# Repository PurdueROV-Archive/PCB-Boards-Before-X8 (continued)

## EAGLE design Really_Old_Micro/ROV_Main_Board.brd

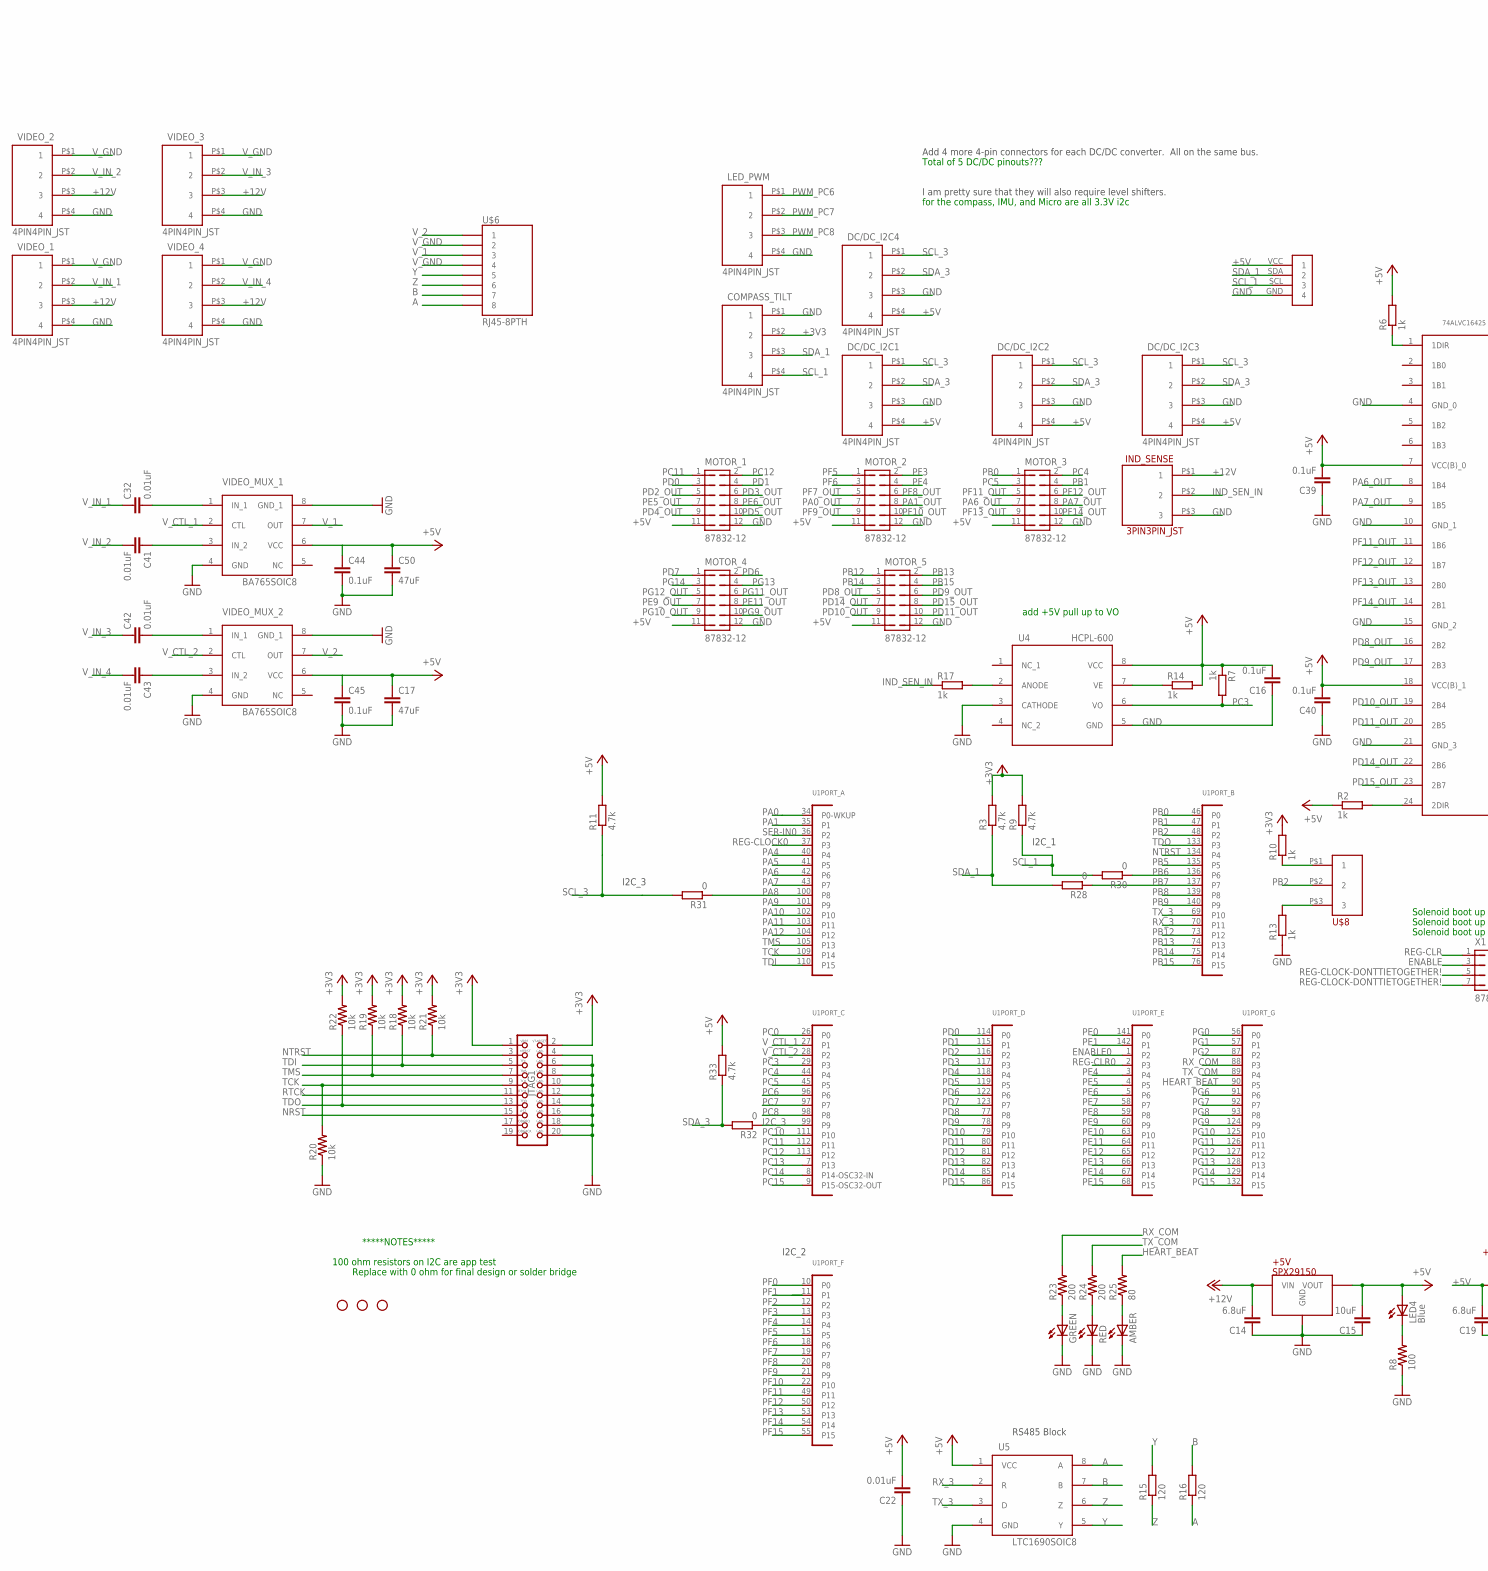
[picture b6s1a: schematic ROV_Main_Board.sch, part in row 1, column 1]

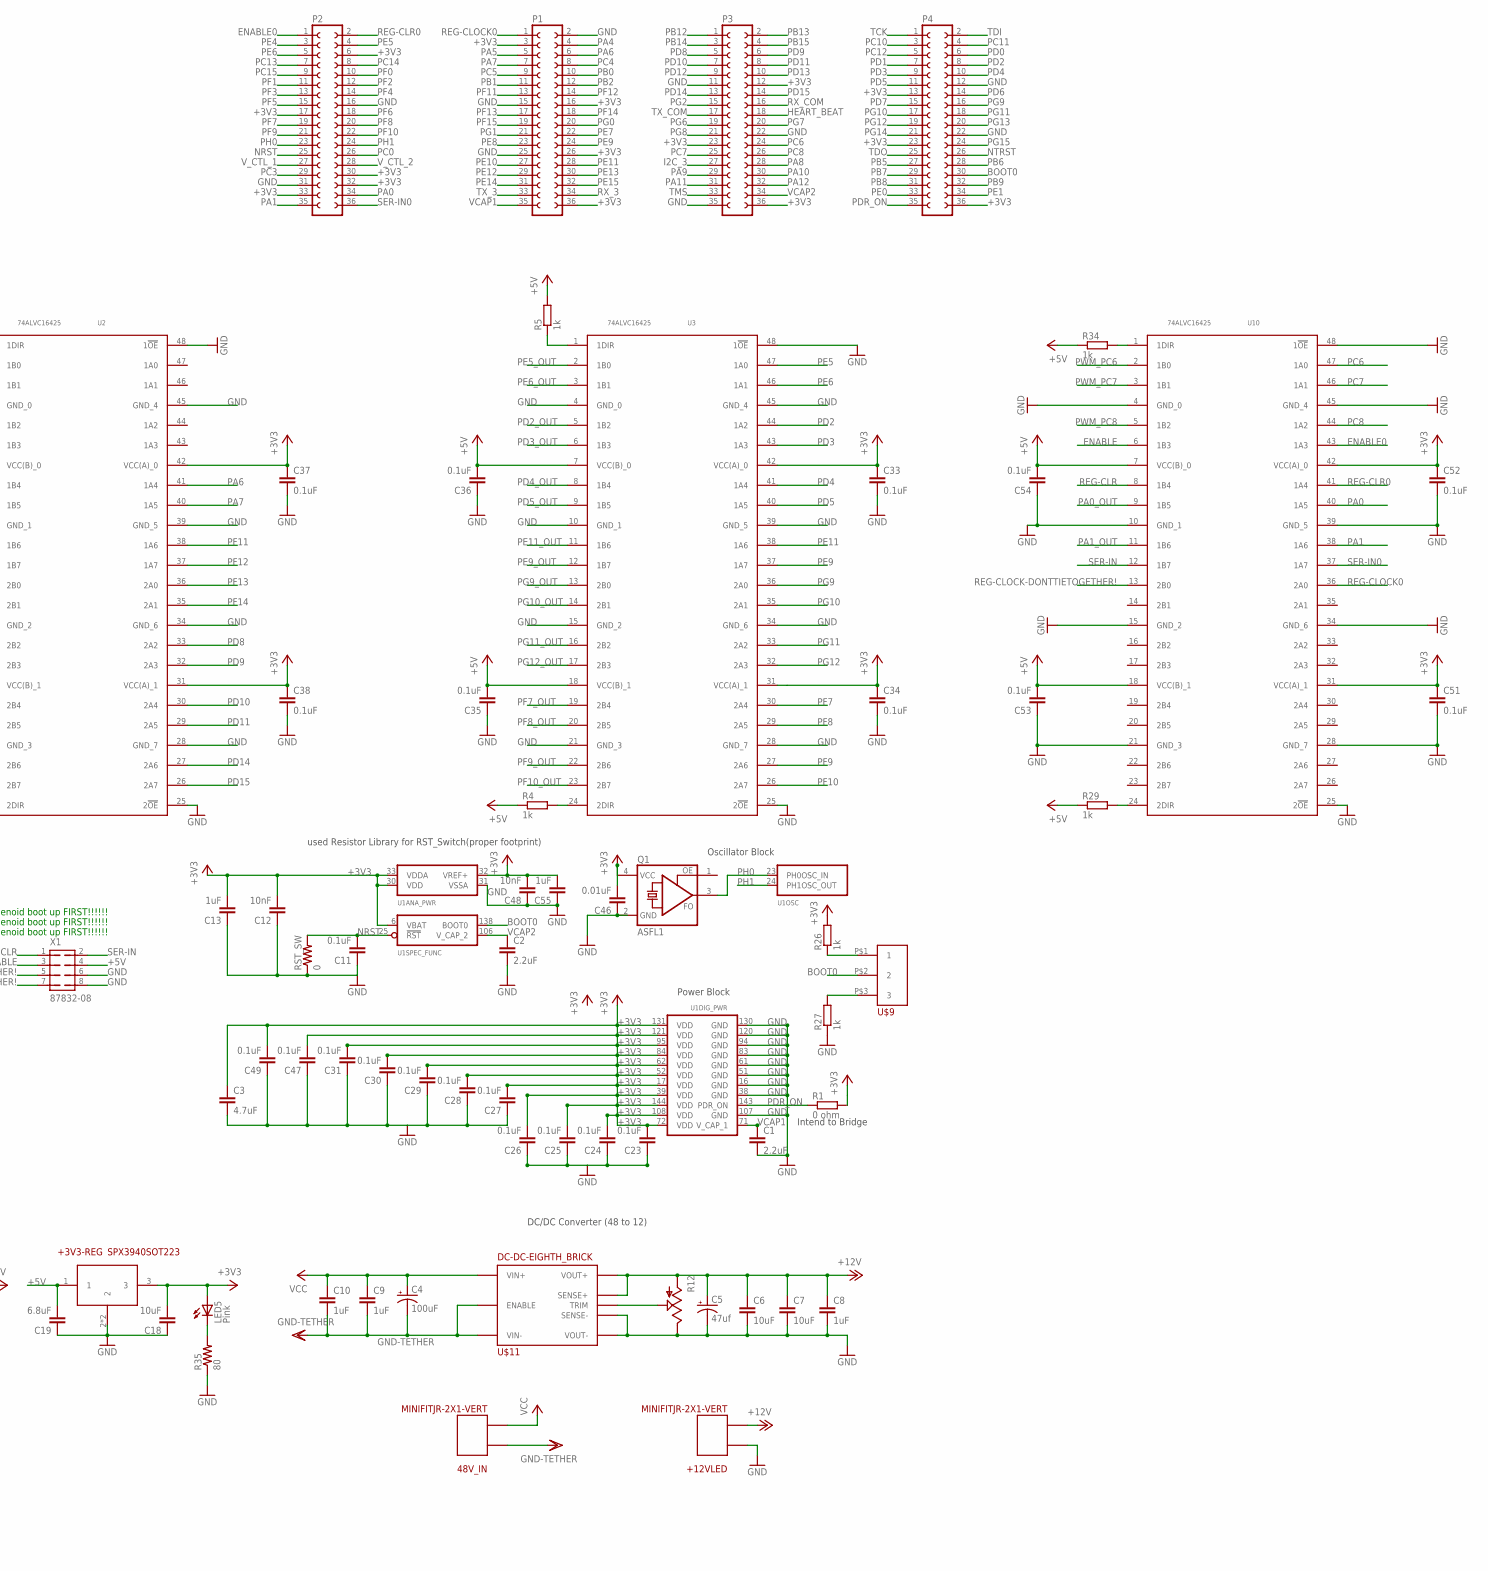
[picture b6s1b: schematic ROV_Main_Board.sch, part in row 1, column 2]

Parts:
48V_IN: MINIFITJR-2X1-VERT; 5566-02B
+3V3-REG: SPX3940SOT223; SOT223
+5V: SPX29150; DDPAK-3PIN
+12VLED: MINIFITJR-2X1-VERT; 5566-02B
AMBER: LED0603; LED-0603
C1, C2: 2.2uF; C0603; PARTNO 587-1263-1-ND
C3: 4.7uF; C0603; PARTNO 587-2786-1-ND
C4: 100uF; E5-10,5; PARTNO 493-1668-ND
C5: 47uf; PANASONIC_D; PARTNO PCE3929CT-ND
C6, C7, C15, C18: 10uF; C0805; PARTNO 587-2985-1-ND
C8, C9, C10: 1uF; C0805; PARTNO 445-5205-1-ND
C11, C16, C23, C24, C25, C26, C27, C28, C29, C30, C31, C33, C34, C35, C36, C37, C38, C39, C40, C44, C45, C47, C49, C51, C52, C53, C54: 0.1uF; C0603; PARTNO 311-1344-1-ND
C12, C48: 10nF; C0603; PARTNO 478-1227-1-ND
C13, C55: 1uF; C0603; PARTNO 445-5205-1-ND
C14, C19: 6.8uF; C0805; PARTNO 445-5982-1-ND
C17, C50: 47uF; C1206; PARTNO 490-5528-1-ND
C22, C32, C41, C42, C43, C46: 0.01uF; C0603; PARTNO 478-1227-1-ND
COMPASS_TILT: 4PIN4PIN_JST; 4PIN_JST; PARTNO 455-1659-ND
DC/DC_I2C1, DC/DC_I2C2, DC/DC_I2C3, DC/DC_I2C4: 4PIN4PIN_JST; 4PIN_JST; PARTNO 455-1659-ND
GREEN: LED0603; LED-0603
IND_SENSE: 3PIN3PIN_JST; 3PIN_JST; PARTNO 455-1658-ND
JP1, JP2, JP3: STAND-OFF
JTAG1: JTAG-ARM; PARTNO S9172-ND
LED4: Blue; LED-0603
LED5: Pink; LED-0603
LED_PWM: 4PIN4PIN_JST; 4PIN_JST; PARTNO 455-1659-ND
MOTOR_1, MOTOR_2, MOTOR_3, MOTOR_4, MOTOR_5: 87832-12; PARTNO WM18640-ND
P1, P2, P3, P4: FE18-2
Q1: ASFL1; ASF
R1: 0 ohm; R0603
R2, R4, R5, R6, R7, R10, R13, R14, R17, R26, R27, R29, R34: 1k; R0603
R3, R9, R11, R33: 4.7k; R0603
R8: 100; 0603-RES
R12: TRIM_US-SM-42/43W; SM-42/43W
R15, R16: 120; R0603
R18, R19, R20, R21, R22: 10k; R0603
R23, R24: 200; R0603
R25: 80; R0603
R28, R30, R31, R32: 0; R0603
R35: 80; 0603-RES
RED: LED0603; LED-0603
RST_SW: 0; R2512
U1: STM32F103ZESTM32F407; SQFP-S-20X20-144
U2, U3, U10: 74ALVC16425; TSSOP48
U4: HCPL-600; SOIC8
U5: LTC1690SOIC8; SOIC8
U$6: RJ45-8PTH; RJ45-8
U$7: 9DOF-IMU-SFE; 9DOF-SFE
U$8, U$9: 1X3-SMD-1.27MM; 1X3-1.27-SMD
U$11: DC-DC-EIGHTH_BRICK; EIGHTH-BRICK
VIDEO_1, VIDEO_2, VIDEO_3, VIDEO_4: 4PIN4PIN_JST; 4PIN_JST
VIDEO_MUX_1, VIDEO_MUX_2: BA765SOIC8; SOIC8
X1: 87832-08

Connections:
+3V3: +3V3-REG.3, C3.1, C12.2, C13.2, C18.2, C23.2, C24.2, C25.2, C26.2, C27.2, C28.2, C29.2, C30.2, C31.2, C33.1, C34.1, C37.1, C38.1, C46.2, C47.2, C48.2, C49.2, C51.1, C52.1, C55.2, COMPASS_TILT.P$2 (2), JTAG1.1, JTAG1.2, LED5.A, P1.3, P1.16, P1.26, P1.36, P2.6, P2.17, P2.30, P2.32, P2.33, P3.12, P3.23, P3.36, P4.13, P4.23, P4.36, Q1.4 (VCC), R1.2, R3.2, R9.2, R10.2, R18.2, R19.2, R21.2, R22.2, R26.2, U1.6 (VBAT), U1.17 (VDD), U1.30 (VDD), U1.32 (VREF+), U1.33 (VDDA), U1.39 (VDD), U1.52 (VDD), U1.62 (VDD), U1.72 (VDD), U1.84 (VDD), U1.95 (VDD), U1.108 (VDD), U1.121 (VDD), U1.131 (VDD), U1.144 (VDD), U2.31 (VCC(A)_1), U2.42 (VCC(A)_0), U3.31 (VCC(A)_1), U3.42 (VCC(A)_0), U10.31 (VCC(A)_1), U10.42 (VCC(A)_0)
+5V: +3V3-REG.1, +5V.P$3 (VOUT), C15.2, C16.2, C17.1, C19.2, C22.2, C35.2, C36.2, C39.2, C40.2, C44.1, C45.1, C50.1, C53.2, C54.2, DC/DC_I2C1.P$4 (4), DC/DC_I2C2.P$4 (4), DC/DC_I2C3.P$4 (4), DC/DC_I2C4.P$4 (4), LED4.A, MOTOR_1.11, MOTOR_2.11, MOTOR_3.11, MOTOR_4.11, MOTOR_5.11, R2.1, R4.1, R5.2, R6.2, R7.1, R11.2, R14.2, R29.1, R33.2, R34.1, U2.7 (VCC(B)_0), U2.18 (VCC(B)_1), U3.7 (VCC(B)_0), U3.18 (VCC(B)_1), U4.8 (VCC), U5.1 (VCC), U10.7 (VCC(B)_0), U10.18 (VCC(B)_1), U$7.VCC (1), VIDEO_MUX_1.6 (VCC), VIDEO_MUX_2.6 (VCC), X1.4
+12V: +5V.P$1 (VIN), +12VLED.P$2, C5.+, C6.1, C7.1, C8.1, C14.2, IND_SENSE.P$1 (1), R12.1 (A), U$11.SENSE(+) (SENSE+), U$11.VOUT(+) (VOUT+), VIDEO_1.P$3 (3), VIDEO_2.P$3 (3), VIDEO_3.P$3 (3), VIDEO_4.P$3 (3)
A: R16.1, U5.8 (A), U$6.8
B: R16.2, U5.7 (B), U$6.7
BOOT0: P4.30, U1.138 (BOOT0), U$9.P$2 (2)
ENABLE: U10.6 (1B3), X1.3
ENABLE0: P2.1, U1.1 (P2), U10.43 (1A3)
GND: +3V3-REG.2, +3V3-REG.4 (2), +5V.P$2 (GND), +5V.P$4 (GND), +12VLED.P$1, AMBER.C, C1.2, C2.2, C3.2, C5.-, C6.2, C7.2, C8.2, C11.1, C12.1, C13.1, C14.1, C15.1, C16.1, C17.2, C18.1, C19.1, C22.1, C23.1, C24.1, C25.1, C26.1, C27.1, C28.1, C29.1, C30.1, C31.1, C33.2, C34.2, C35.1, C36.1, C37.2, C38.2, C39.1, C40.1, C44.2, C45.2, C46.1, C47.1, C48.1, C49.1, C50.2, C51.2, C52.2, C53.1, C54.1, C55.1, COMPASS_TILT.P$1 (1), DC/DC_I2C1.P$3 (3), DC/DC_I2C2.P$3 (3), DC/DC_I2C3.P$3 (3), DC/DC_I2C4.P$3 (3), GREEN.C, IND_SENSE.P$3 (3), JTAG1.4, JTAG1.6, JTAG1.8, JTAG1.10, JTAG1.12, JTAG1.14, JTAG1.16, JTAG1.18, JTAG1.20, LED_PWM.P$4 (4), MOTOR_1.12, MOTOR_2.12, MOTOR_3.12, MOTOR_4.12, MOTOR_5.12, P1.2, P1.15, P1.25, P2.16, P2.31, P3.11, P3.22, P3.35, P4.12, P4.22, Q1.2 (GND), R8.1, R12.3 (E), R13.1, R20.1, R27.1, R35.1, RED.C, RST_SW.1, U1.16 (GND), U1.31 (VSSA), U1.38 (GND), U1.51 (GND), U1.61 (GND), U1.83 (GND), U1.94 (GND), U1.107 (GND), U1.120 (GND), U1.130 (GND), U2.4 (GND_0), U2.10 (GND_1), U2.15 (GND_2), U2.21 (GND_3), U2.25 (2!OE), U2.28 (GND_7), U2.34 (GND_6), U2.39 (GND_5), U2.45 (GND_4), U2.48 (1!OE), U3.4 (GND_0), U3.10 (GND_1), U3.15 (GND_2), U3.21 (GND_3), U3.25 (2!OE), U3.28 (GND_7), U3.34 (GND_6), U3.39 (GND_5), U3.45 (GND_4), U3.48 (1!OE), U4.3 (CATHODE), U4.5 (GND), U5.4 (GND), U10.4 (GND_0), U10.10 (GND_1), U10.15 (GND_2), U10.21 (GND_3), U10.25 (2!OE), U10.28 (GND_7), U10.34 (GND_6), U10.39 (GND_5), U10.45 (GND_4), U10.48 (1!OE), U$7.GND (4), U$11.SENSE(-) (SENSE-), U$11.VOUT(-) (VOUT-), VIDEO_1.P$4 (4), VIDEO_2.P$4 (4), VIDEO_3.P$4 (4), VIDEO_4.P$4 (4), VIDEO_MUX_1.4 (GND), VIDEO_MUX_1.8 (GND_1), VIDEO_MUX_2.4 (GND), VIDEO_MUX_2.8 (GND_1), X1.6, X1.8
GND-TETHER: 48V_IN.P$1, C4.-, C9.2, C10.2, U$11.ENABLE, U$11.VIN(-) (VIN-)
HEART_BEAT: P3.18, R25.2, U1.90 (P5)
I2C_3: P3.27, R32.1, U1.99 (P9)
IND_SEN_IN: IND_SENSE.P$2 (2), R17.1
unnamed: R12.2 (S), U$11.TRIM
unnamed: LED4.C, R8.2
unnamed: R26.1, U$9.P$1 (1)
unnamed: LED5.C, R35.2
unnamed: R14.1, U4.7 (VE)
unnamed: R17.2, U4.2 (ANODE)
unnamed: GREEN.A, R23.1
unnamed: R24.1, RED.A
unnamed: C32.2, VIDEO_MUX_1.1 (IN_1)
unnamed: AMBER.A, R25.1
unnamed: C41.1, VIDEO_MUX_1.3 (IN_2)
unnamed: C42.2, VIDEO_MUX_2.1 (IN_1)
unnamed: C43.1, VIDEO_MUX_2.3 (IN_2)
unnamed: R29.2, U10.24 (2DIR)
unnamed: R27.2, U$9.P$3 (3)
unnamed: R6.1, U2.1 (1DIR)
unnamed: R5.1, U3.1 (1DIR)
unnamed: R4.2, U3.24 (2DIR)
unnamed: R2.2, U2.24 (2DIR)
unnamed: R10.1, U$8.P$1 (1)
unnamed: R13.2, U$8.P$3 (3)
unnamed: R34.2, U10.1 (1DIR)
NRST: C11.2, JTAG1.15, P2.25, RST_SW.2, U1.25 (!RST)
NTRST: JTAG1.3, P4.26, R21.1, U1.134 (P4)
PA0: P2.34, U1.34 (P0-WKUP), U10.40 (1A5)
PA0_OUT: MOTOR_2.7, U10.9 (1B5)
PA1: P2.35, U1.35 (P1), U10.38 (1A6)
PA1_OUT: MOTOR_2.8, U10.11 (1B6)
PA4: P1.4, U1.40 (P4)
PA5: P1.5, U1.41 (P5)
PA6: P1.6, U1.42 (P6), U2.41 (1A4)
PA6_OUT: MOTOR_3.7, U2.8 (1B4)
PA7: P1.7, U1.43 (P7), U2.40 (1A5)
PA7_OUT: MOTOR_3.8, U2.9 (1B5)
PA8: P3.28, R31.1, U1.100 (P8)
PA9: P3.29, U1.101 (P9)
PA10: P3.30, U1.102 (P10)
PA11: P3.31, U1.103 (P11)
PA12: P3.32, U1.104 (P12)
PB0: MOTOR_3.1, P1.10, U1.46 (P0)
PB1: MOTOR_3.4, P1.11, U1.47 (P1)
PB2: P1.12, U1.48 (P2), U$8.P$2 (2)
PB5: P4.27, U1.135 (P5)
PB6: P4.28, R30.1, U1.136 (P6)
PB7: P4.29, R28.1, U1.137 (P7)
PB8: P4.31, U1.139 (P8)
PB9: P4.32, U1.140 (P9)
PB12: MOTOR_5.1, P3.1, U1.73 (P12)
PB13: MOTOR_5.2, P3.2, U1.74 (P13)
PB14: MOTOR_5.3, P3.3, U1.75 (P14)
PB15: MOTOR_5.4, P3.4, U1.76 (P15)
PC0: P2.26, U1.26 (P0)
PC3: P2.29, R7.2, U1.29 (P3), U4.6 (VO)
PC4: MOTOR_3.2, P1.8, U1.44 (P4)
PC5: MOTOR_3.3, P1.9, U1.45 (P5)
PC6: P3.24, U1.96 (P6), U10.47 (1A0)
PC7: P3.25, U1.97 (P7), U10.46 (1A1)
PC8: P3.26, U1.98 (P8), U10.44 (1A2)
PC10: P4.3, U1.111 (P10)
PC11: MOTOR_1.1, P4.4, U1.112 (P11)
PC12: MOTOR_1.2, P4.5, U1.113 (P12)
PC13: P2.7, U1.7 (P13)
PC14: P2.8, U1.8 (P14-OSC32-IN)
PC15: P2.9, U1.9 (P15-OSC32-OUT)
PD0: MOTOR_1.3, P4.6, U1.114 (P0)
PD1: MOTOR_1.4, P4.7, U1.115 (P1)
PD2: P4.8, U1.116 (P2), U3.44 (1A2)
PD2_OUT: MOTOR_1.5, U3.5 (1B2)
PD3: P4.9, U1.117 (P3), U3.43 (1A3)
PD3_OUT: MOTOR_1.6, U3.6 (1B3)
PD4: P4.10, U1.118 (P4), U3.41 (1A4)
PD4_OUT: MOTOR_1.9, U3.8 (1B4)
PD5: P4.11, U1.119 (P5), U3.40 (1A5)
PD5_OUT: MOTOR_1.10, U3.9 (1B5)
PD6: MOTOR_4.2, P4.14, U1.122 (P6)
PD7: MOTOR_4.1, P4.15, U1.123 (P7)
PD8: P3.5, U1.77 (P8), U2.33 (2A2)
PD8_OUT: MOTOR_5.5, U2.16 (2B2)
PD9: P3.6, U1.78 (P9), U2.32 (2A3)
PD9_OUT: MOTOR_5.6, U2.17 (2B3)
PD10: P3.7, U1.79 (P10), U2.30 (2A4)
PD10_OUT: MOTOR_5.9, U2.19 (2B4)
PD11: P3.8, U1.80 (P11), U2.29 (2A5)
PD11_OUT: MOTOR_5.10, U2.20 (2B5)
PD12: P3.9, U1.81 (P12)
PD13: P3.10, U1.82 (P13)
PD14: P3.13, U1.85 (P14), U2.27 (2A6)
PD14_OUT: MOTOR_5.7, U2.22 (2B6)
PD15: P3.14, U1.86 (P15), U2.26 (2A7)
PD15_OUT: MOTOR_5.8, U2.23 (2B7)
PDR_ON: P4.35, R1.1, U1.143 (PDR_ON)
PE0: P4.33, U1.141 (P0)
PE1: P4.34, U1.142 (P1)
PE4: P2.3, U1.3 (P4)
PE5: P2.4, U1.4 (P5), U3.47 (1A0)
PE5_OUT: MOTOR_1.7, U3.2 (1B0)
PE6: P2.5, U1.5 (P6), U3.46 (1A1)
PE6_OUT: MOTOR_1.8, U3.3 (1B1)
PE7: P1.22, U1.58 (P7)
PE8: P1.23, U1.59 (P8)
PE9: P1.24, U1.60 (P9), U3.37 (1A7)
PE9_OUT: MOTOR_4.7, U3.12 (1B7)
PE10: P1.27, U1.63 (P10)
PE11: P1.28, U1.64 (P11), U3.38 (1A6)
PE11_OUT: MOTOR_4.8, U3.11 (1B6)
PE12: P1.29, U1.65 (P12)
PE13: P1.30, U1.66 (P13)
PE14: P1.31, U1.67 (P14)
PE15: P1.32, U1.68 (P15)
PF0: P2.10, U1.10 (P0)
PF1: P2.11, U1.11 (P1)
PF2: P2.12, U1.12 (P2)
PF3: MOTOR_2.2, P2.13, U1.13 (P3)
PF4: MOTOR_2.4, P2.14, U1.14 (P4)
PF5: MOTOR_2.1, P2.15, U1.15 (P5)
PF6: MOTOR_2.3, P2.18, U1.18 (P6)
PF7: P2.19, U1.19 (P7), U3.30 (2A4)
PF7_OUT: MOTOR_2.5, U3.19 (2B4)
PF8: P2.20, U1.20 (P8), U3.29 (2A5)
PF8_OUT: MOTOR_2.6, U3.20 (2B5)
PF9: P2.21, U1.21 (P9), U3.27 (2A6)
PF9_OUT: MOTOR_2.9, U3.22 (2B6)
PF10: P2.22, U1.22 (P10), U3.26 (2A7)
PF10_OUT: MOTOR_2.10, U3.23 (2B7)
PF11: P1.13, U1.49 (P11), U2.38 (1A6)
PF11_OUT: MOTOR_3.5, U2.11 (1B6)
PF12: P1.14, U1.50 (P12), U2.37 (1A7)
PF12_OUT: MOTOR_3.6, U2.12 (1B7)
PF13: P1.17, U1.53 (P13), U2.36 (2A0)
PF13_OUT: MOTOR_3.9, U2.13 (2B0)
PF14: P1.18, U1.54 (P14), U2.35 (2A1)
PF14_OUT: MOTOR_3.10, U2.14 (2B1)
PF15: P1.19, U1.55 (P15)
PG0: P1.20, U1.56 (P0)
PG1: P1.21, U1.57 (P1)
PG2: P3.15, U1.87 (P2)
PG6: P3.19, U1.91 (P6)
PG7: P3.20, U1.92 (P7)
PG8: P3.21, U1.93 (P8)
PG9: P4.16, U1.124 (P9), U3.36 (2A0)
PG9_OUT: MOTOR_4.10, U3.13 (2B0)
PG10: P4.17, U1.125 (P10), U3.35 (2A1)
PG10_OUT: MOTOR_4.9, U3.14 (2B1)
PG11: P4.18, U1.126 (P11), U3.33 (2A2)
PG11_OUT: MOTOR_4.6, U3.16 (2B2)
PG12: P4.19, U1.127 (P12), U3.32 (2A3)
PG12_OUT: MOTOR_4.5, U3.17 (2B3)
PG13: MOTOR_4.4, P4.20, U1.128 (P13)
PG14: MOTOR_4.3, P4.21, U1.129 (P14)
PG15: P4.24, U1.132 (P15)
PH0: P2.23, Q1.3 (FO), U1.23 (PH0OSC_IN)
PH1: P2.24, U1.24 (PH1OSC_OUT)
PWM_PC6: LED_PWM.P$1 (1), U10.2 (1B0)
PWM_PC7: LED_PWM.P$2 (2), U10.3 (1B1)
PWM_PC8: LED_PWM.P$3 (3), U10.5 (1B2)
REG-CLOCK0: P1.1, U1.37 (P3), U10.36 (2A0)
REG-CLOCK-DONTTIETOGETHER!: U10.13 (2B0), X1.5, X1.7
REG-CLR: U10.8 (1B4), X1.1
REG-CLR0: P2.2, U1.2 (P3), U10.41 (1A4)
RTCK: JTAG1.11
RX_3: P1.34, U1.70 (P11), U5.2 (R)
RX_COM: P3.16, R23.2, U1.88 (P3)
SCL_1: COMPASS_TILT.P$4 (4), R9.1, R30.2, U$7.SCL (3)
SCL_3: DC/DC_I2C1.P$1 (1), DC/DC_I2C2.P$1 (1), DC/DC_I2C3.P$1 (1), DC/DC_I2C4.P$1 (1), R11.1, R31.2
SDA_1: COMPASS_TILT.P$3 (3), R3.1, R28.2, U$7.SDA (2)
SDA_3: DC/DC_I2C1.P$2 (2), DC/DC_I2C2.P$2 (2), DC/DC_I2C3.P$2 (2), DC/DC_I2C4.P$2 (2), R32.2, R33.1
SER-IN: U10.12 (1B7), X1.2
SER-IN0: P2.36, U1.36 (P2), U10.37 (1A7)
TCK: JTAG1.9, P4.1, R20.2, U1.109 (P14)
TDI: JTAG1.5, P4.2, R18.1, U1.110 (P15)
TDO: JTAG1.13, P4.25, R22.1, U1.133 (P3)
TMS: JTAG1.7, P3.33, R19.1, U1.105 (P13)
TX_3: P1.33, U1.69 (P10), U5.3 (D)
TX_COM: P3.17, R24.2, U1.89 (P4)
VCAP1: C1.1, P1.35, U1.71 (V_CAP_1)
VCAP2: C2.1, P3.34, U1.106 (V_CAP_2)
VCC: 48V_IN.P$2, C4.+, C9.1, C10.1, U$11.VIN(+) (VIN+)
V_1: U$6.3, VIDEO_MUX_1.7 (OUT)
V_2: U$6.1, VIDEO_MUX_2.7 (OUT)
V_CTL_1: P2.27, U1.27 (P1), VIDEO_MUX_1.2 (CTL)
V_CTL_2: P2.28, U1.28 (P2), VIDEO_MUX_2.2 (CTL)
V_GND: U$6.2, U$6.4, VIDEO_1.P$1 (1), VIDEO_2.P$1 (1), VIDEO_3.P$1 (1), VIDEO_4.P$1 (1)
V_IN_1: C32.1, VIDEO_1.P$2 (2)
V_IN_2: C41.2, VIDEO_2.P$2 (2)
V_IN_3: C42.1, VIDEO_3.P$2 (2)
V_IN_4: C43.2, VIDEO_4.P$2 (2)
Y: R15.2, U5.5 (Y), U$6.5
Z: R15.1, U5.6 (Z), U$6.6

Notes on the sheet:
used Resistor Library for RST_Switch(proper footprint)
I2C_2
I2C_1
I2C_3
Power Block
RS485 Block
Oscillator Block
DC/DC Converter (48 to 12)
add +5V pull up to VO
Solenoid boot up FIRST!!!!!!
Add 4 more 4-pin connectors for each DC/DC converter. All on the same bus.
I am pretty sure that they will also require level shifters.
Total of 5 DC/DC pinouts???
for the compass, IMU, and Micro are all 3.3V i2c
*****NOTES*****
100 ohm resistors on I2C are app test
Replace with 0 ohm for final design or solder bridge
Intend to Bridge

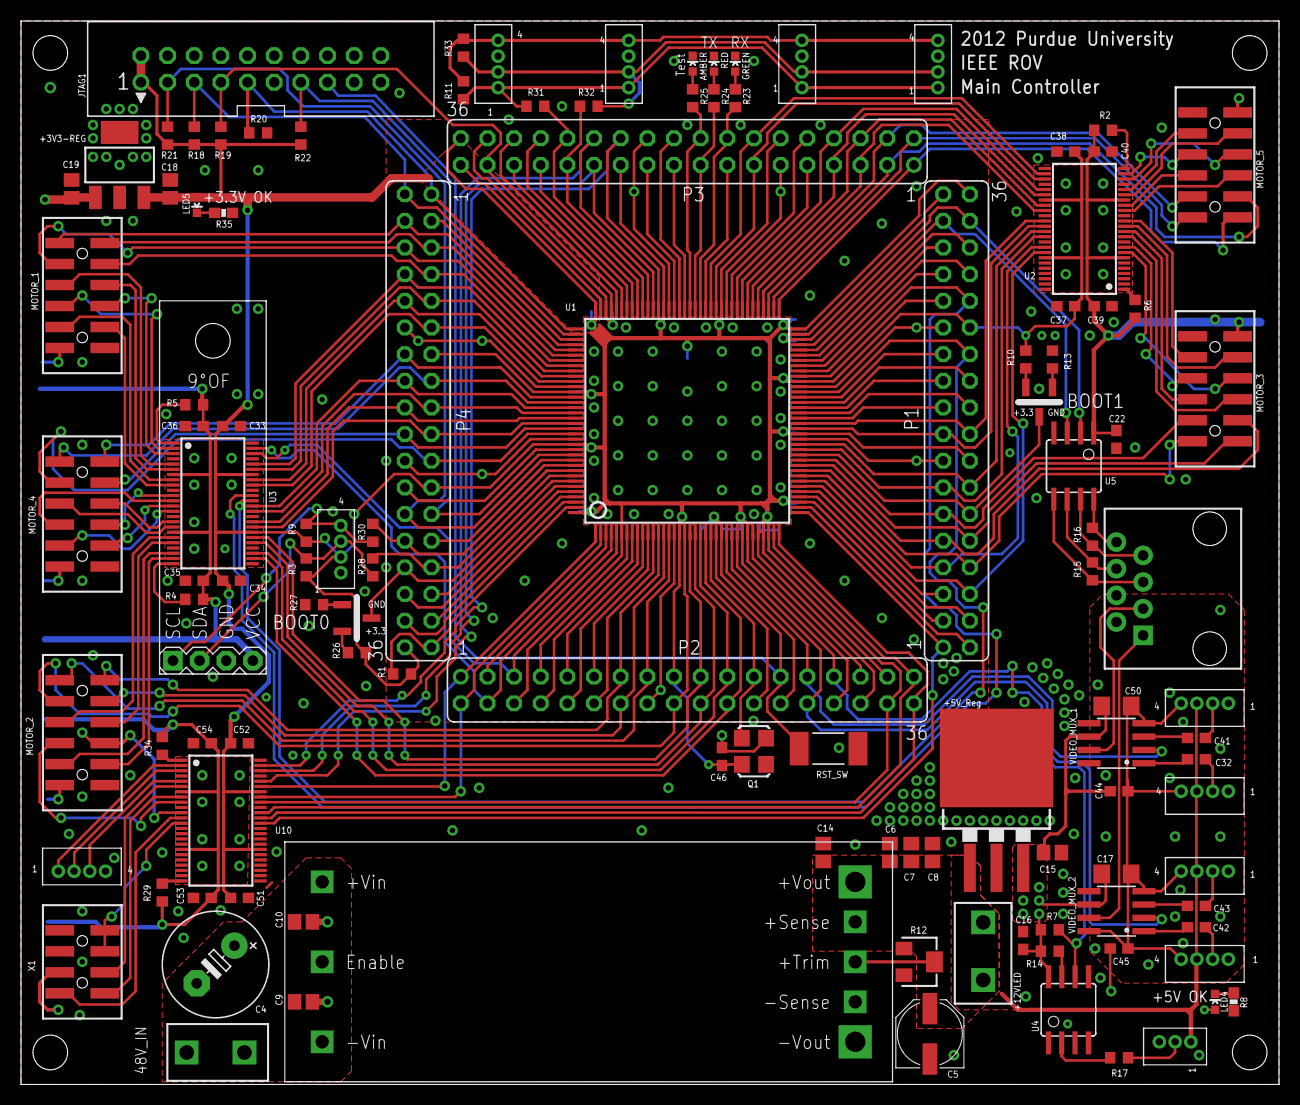
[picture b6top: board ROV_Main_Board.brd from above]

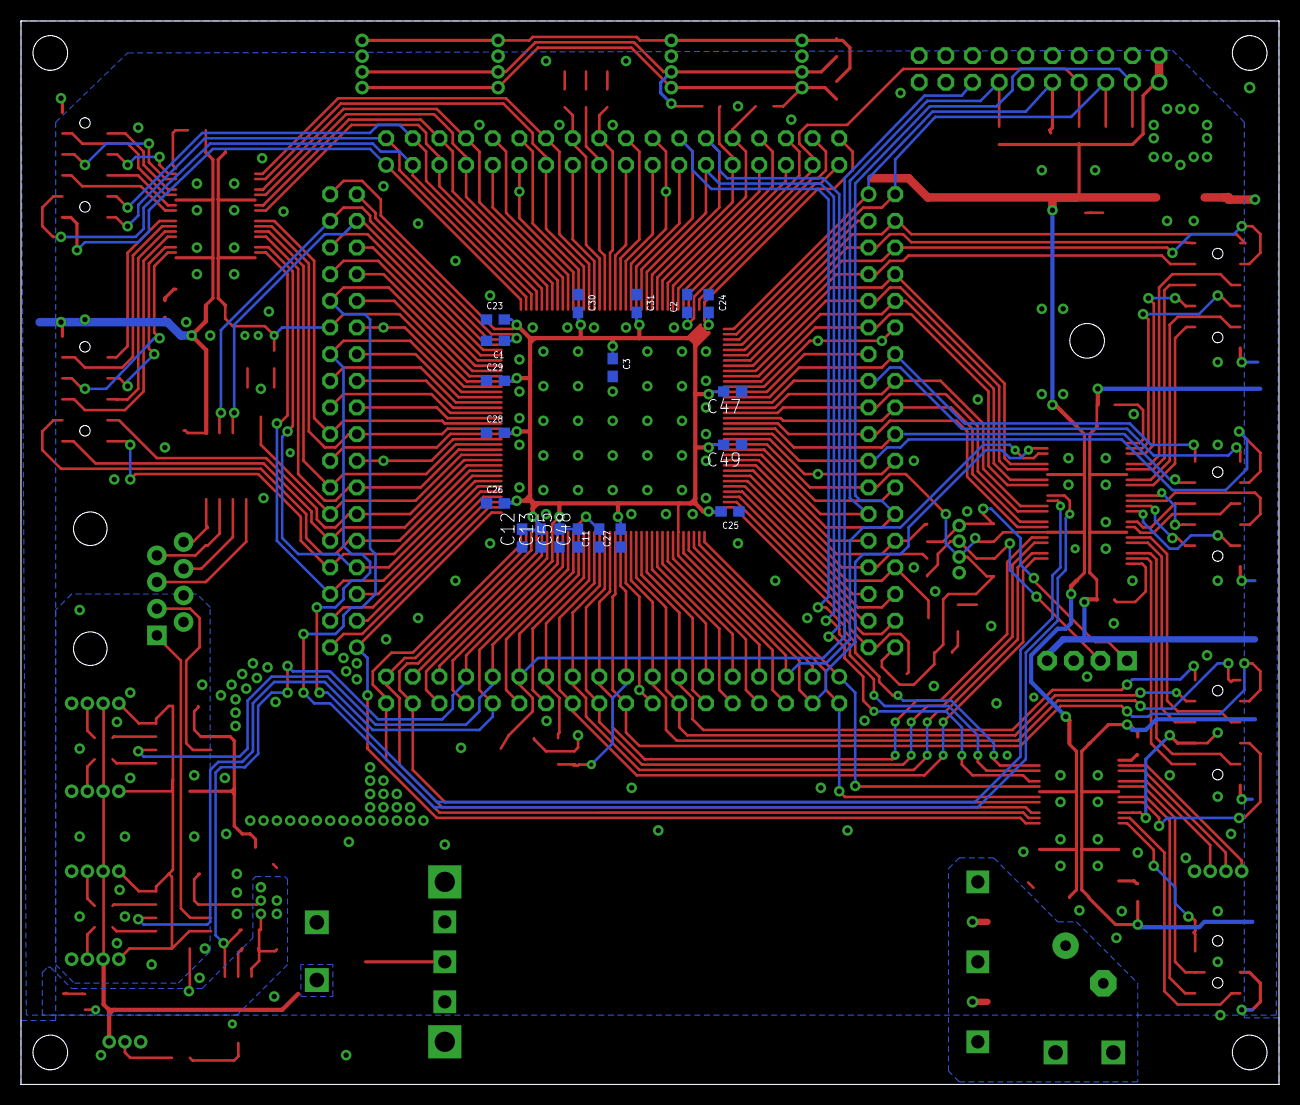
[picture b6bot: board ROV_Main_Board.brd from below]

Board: 2 copper layers, 119.9 x 101.3 mm, 138 parts (19 on the bottom side), 200 nets.

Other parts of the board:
JP4: STAND-OFF

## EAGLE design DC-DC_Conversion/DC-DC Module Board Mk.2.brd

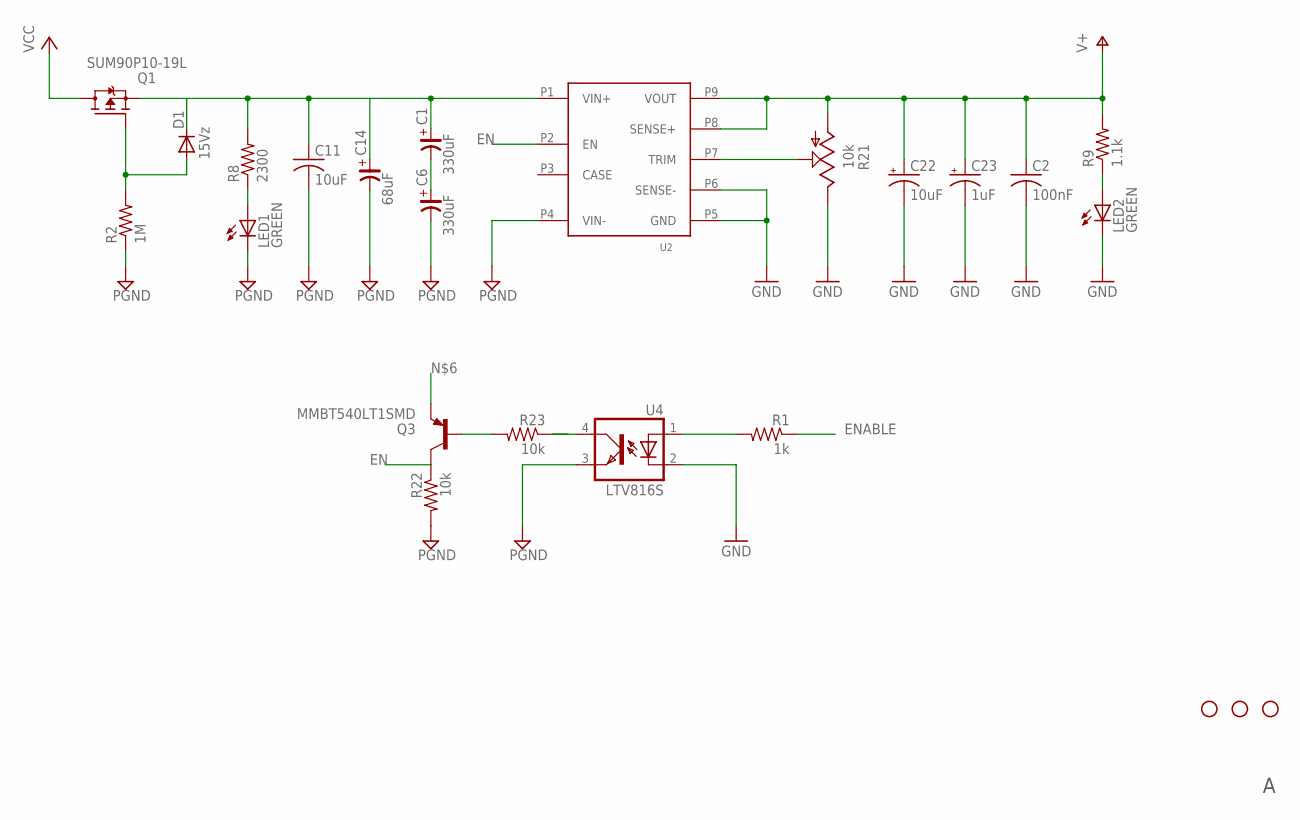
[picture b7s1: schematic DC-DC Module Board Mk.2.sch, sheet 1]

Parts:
C1, C6: 330uF; CSV-H; PARTNO 338-2190-1-ND
C2: 100nF; C0603; PARTNO 445-5202-1-ND
C11: 10uF; C2220K; PARTNO 445-5212-1-ND
C14: 68uF; CSV-H; PARTNO 565-2343-1-ND
C22: 10uF; EIA7343; PARTNO 399-3893-1-ND
C23: 1uF; EIA3528; PARTNO 478-6247-1-ND
D1: 15Vz; SOD123; PARTNO MMSZ5245BFSCT-ND
JP1, JP2, JP4: STAND-OFF
LED1, LED2: GREEN; LED-0603; PARTNO 160-1446-1-ND
Q1: SUM90P10-19L; TO263; PARTNO SUM90P10-19L-E3CT-ND
Q3: MMBT540LT1SMD; SOT23-BEC; PARTNO MMBT5401FSCT-ND
R1: 1k; R0603; PARTNO P1.00KHCT-ND
R2: 1M; R0603; PARTNO 1.00MHCT-ND
R8: 2300; R2512; PARTNO RHC2512FT2K20CT-ND
R9: 1.1k; R1206; PARTNO RNCP1206FTD1K10CT-ND
R21: 10k; SM-42/43W; PARTNO SM-43TW103CT-ND
R22, R23: 10k; R0603; PARTNO P10.0KHCT-ND
U2: CHB350-24V; CHB350HALFBRICK
U4: LTV816S; SMD4; PARTNO 160-1361-5-ND

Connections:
EN: Q3.C, R22.1, U2.P2 (EN)
ENABLE: R1.1; also elsewhere on the board
GND: C2.2, C22.C (-), C23.C (-), LED2.C, R21.3 (E), U2.P5 (GND), U2.P6 (SENSE-), U4.2 (C); also elsewhere on the board
GND1: C6.-, C11.2, C14.-, LED1.C, R2.1, R22.2, U2.P4 (VIN-), U4.3 (EMIT); also elsewhere on the board
unnamed: R1.2, U4.1 (A)
unnamed: C1.-, C6.+
unnamed: D1.A, Q1.1 (G), R2.2
unnamed: C1.+, C11.1, C14.+, D1.C, Q1.2 (S), Q3.E, R8.2, U2.P1 (VIN+)
unnamed: LED2.A, R9.1
unnamed: LED1.A, R8.1
unnamed: R21.2 (S), U2.P7 (TRIM)
unnamed: R23.1, U4.4 (COL)
unnamed: Q3.B, R23.2
V+: C2.1, C22.A (+), C23.A (+), R9.2, R21.1 (A), U2.P8 (SENSE+), U2.P9 (VOUT); also elsewhere on the board
VCC: Q1.3 (D); also elsewhere on the board

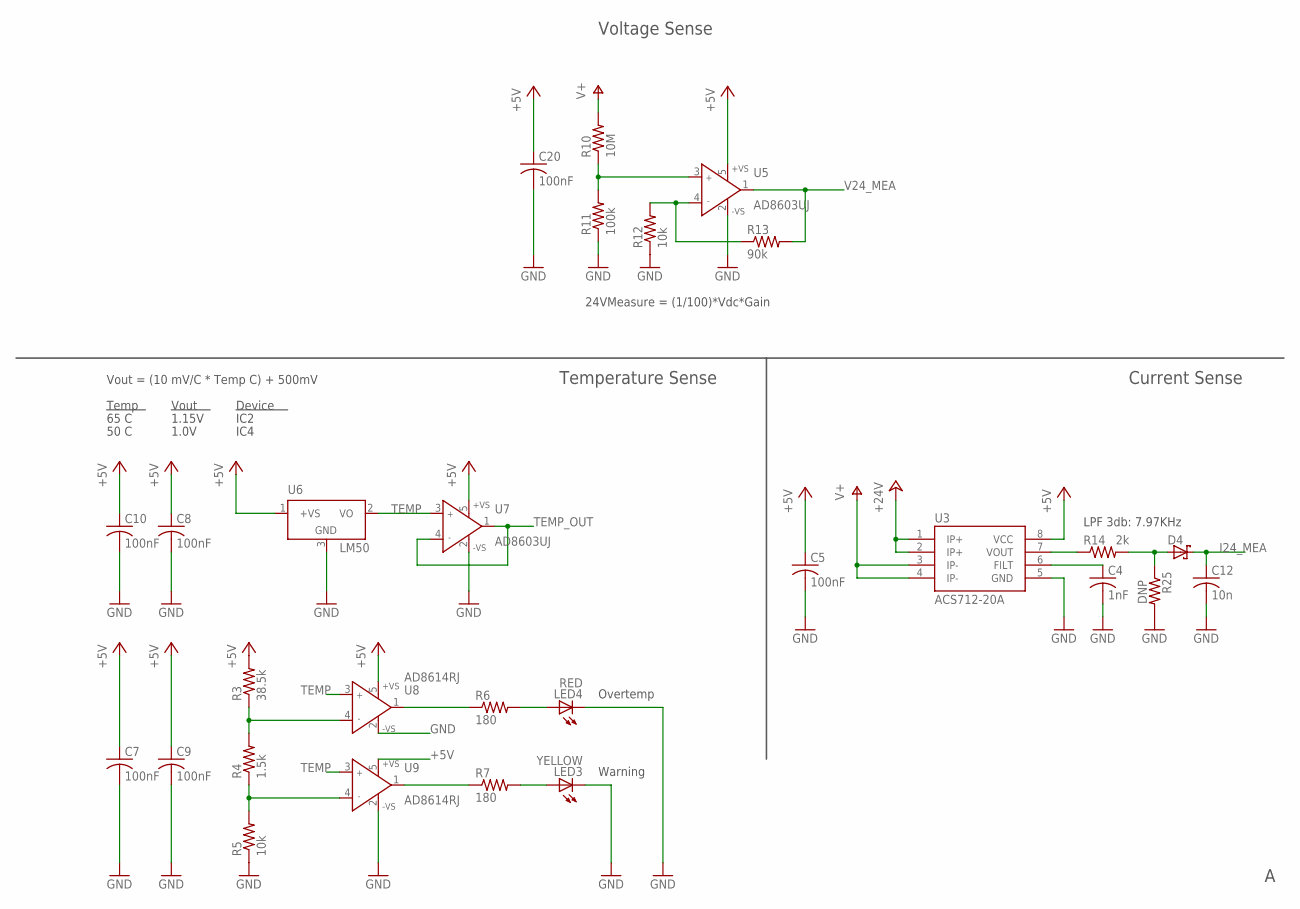
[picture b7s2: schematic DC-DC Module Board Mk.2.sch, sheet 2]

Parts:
C4: 1nF; C0603; PARTNO 490-1472-1-ND
C5, C7, C8, C9, C10, C20: 100nF; C0603; PARTNO 445-5202-1-ND
C12: 10n; C0603; PARTNO 445-1304-1-ND
D4: BAT54; SOT23; PARTNO BAT54FSCT-ND
LED3: YELLOW; LED-0603; PARTNO 160-1447-1-ND
LED4: RED; LED-0603; PARTNO 160-1448-1-ND
R3: 38.5k; R0603; PARTNO P33.2KHCT-ND
R4: 1.5k; R0603; PARTNO P2.70KHCT-ND
R5, R12: 10k; R0603; PARTNO P10.0KHCT-ND
R6, R7: 180; R0603; PARTNO P82.0HCT-ND
R10: 10M; R0603; PARTNO P10MGCT-ND
R11: 100k; R0603; PARTNO P100KHCT-ND
R13: 90k; R0603; PARTNO P90.9KHCT-ND
R14: 2k; R0603; PARTNO P2.00KHCT-ND
R25: DNP; R0603; PARTNO P2.00KHCT-ND
U3: ACS712-20A; SO08; PARTNO 620-1190-1-ND
U5, U7: AD8603UJ; SOT23-5; PARTNO AD8603AUJZREEL7CT-ND
U6: LM50; SOT23; PARTNO LM50CIM3CT-ND
U8, U9: AD8614RJ; SOT23-5; PARTNO AD8614ARTZ-REEL7CT-ND

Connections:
+5V: C5.1, C7.1, C8.1, C9.1, C10.1, C20.1, R3.2, U3.8 (VCC), U5.5 (+VS), U6.1 (+VS), U7.5 (+VS), U8.5 (+VS), U9.5 (+VS); also elsewhere on the board
+24V: U3.1 (IP+), U3.2 (IP+); also elsewhere on the board
GND: C4.2, C5.2, C7.2, C8.2, C9.2, C10.2, C12.2, C20.2, LED3.C, LED4.C, R5.1, R11.1, R12.1, R25.2, U3.5 (GND), U5.2 (-VS), U6.3 (GND), U7.2 (-VS), U8.2 (-VS), U9.2 (-VS); also elsewhere on the board
I24_MEA: C12.1, D4.3 (C); also elsewhere on the board
unnamed: C4.1, U3.6 (FILT)
unnamed: R3.1, R4.2, U8.4 (IN-)
unnamed: R4.1, R5.2, U9.4 (IN-)
unnamed: LED4.A, R6.2
unnamed: LED3.A, R7.2
unnamed: R6.1, U8.1 (OUT)
unnamed: R7.1, U9.1 (OUT)
unnamed: R12.2, R13.1, U5.4 (IN-)
unnamed: R10.1, R11.2, U5.3 (IN+)
unnamed: D4.1 (A), R14.2, R25.1
unnamed: R14.1, U3.7 (VOUT)
TEMP: U6.2 (VO), U7.3 (IN+), U8.3 (IN+), U9.3 (IN+)
TEMP_OUT: U7.1 (OUT), U7.4 (IN-); also elsewhere on the board
V24_MEA: R13.2, U5.1 (OUT); also elsewhere on the board
V+: R10.2, U3.3 (IP-), U3.4 (IP-); also elsewhere on the board

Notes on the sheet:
Vout = (10 mV/C * Temp C) + 500mV
Vout
Temp
65 C
50 C
1.15V
1.0V
Device
IC2
IC4
Warning
Overtemp
24VMeasure = (1/100)*Vdc*Gain
Temperature Sense
Current Sense
Voltage Sense
LPF 3db: 7.97KHz

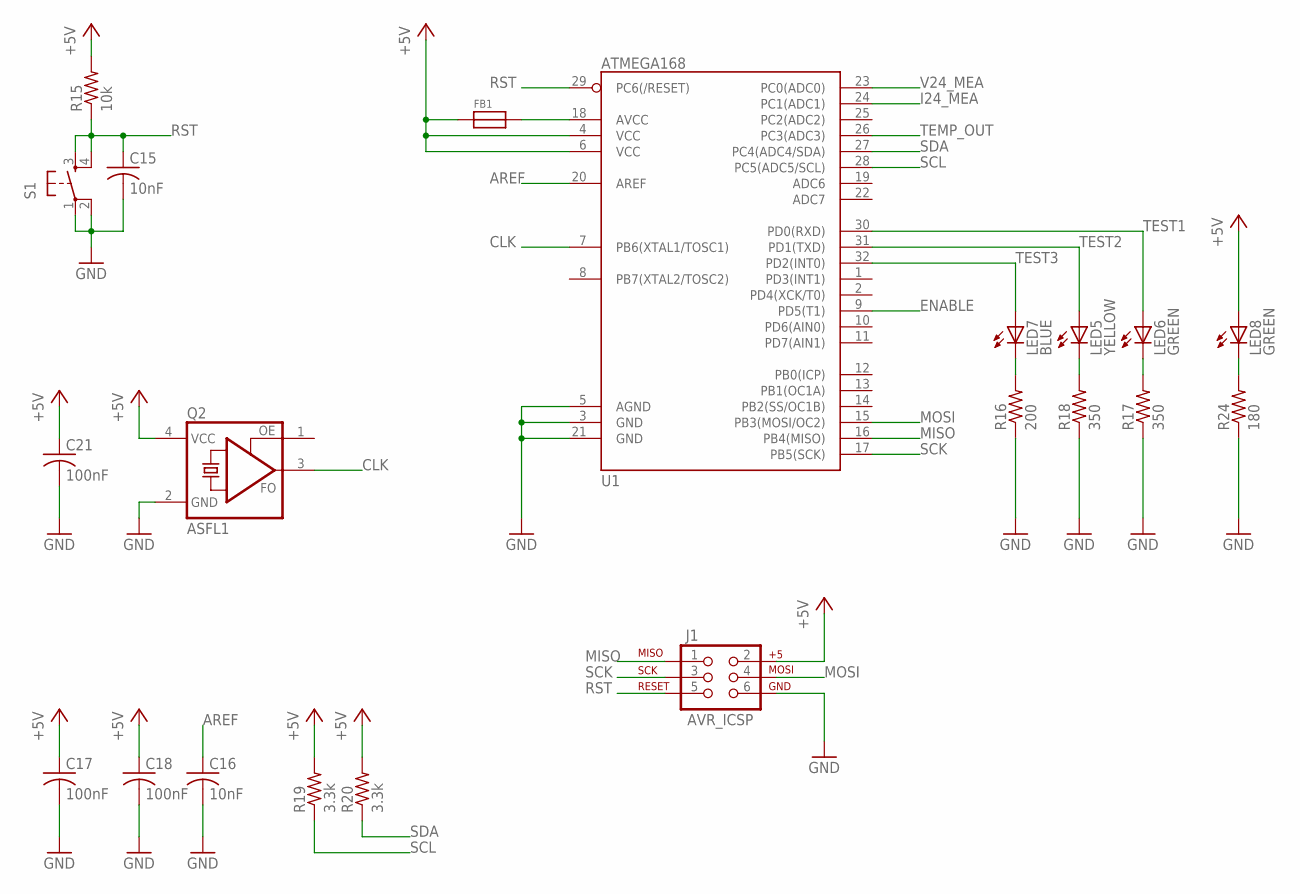
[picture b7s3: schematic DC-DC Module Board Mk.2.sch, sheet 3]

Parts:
C15, C16: 10nF; C0603; PARTNO 445-1304-1-ND
C17, C18: 100nF; C0603; PARTNO 445-5202-1-ND
C21: 100nF; C0603; PARTNO 445-5047-1-ND
FB1: FERRITE; 0603; PARTNO 445-2164-1-ND
J1: AVR_ICSP; 2X3_LOCK
LED5: YELLOW; LED-0603; PARTNO 160-1448-1-ND
LED6, LED8: GREEN; LED-0603; PARTNO 160-1446-1-ND
LED7: BLUE; LED-0603; PARTNO 160-1647-1-ND
Q2: ASFL1; ASF; PARTNO XC1900CT-ND
R15: 10k; R0603; PARTNO P10.0KHCT-ND
R16: 200; R0603; PARTNO P200HCT-ND
R17, R18: 350; R0603; PARTNO P340HCT-ND
R19, R20: 3.3k; R0603; PARTNO P33.0KHCT-ND
R24: 180; R0603; PARTNO P180HCT-ND
S1: TAC_SWITCHSMD; TACTILE_SWITCH_SMD; PARTNO COM-08720
U1: ATMEGA168; TQFP32-08; PARTNO ATMEGA168-20AU-ND

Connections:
+5V: C17.1, C18.1, C21.1, FB1.1, J1.2, LED8.A, Q2.4 (VCC), R15.2, R19.2, R20.2, U1.4 (VCC), U1.6 (VCC); also elsewhere on the board
AREF: C16.1, U1.20 (AREF)
CLK: Q2.3 (FO), U1.7 (PB6(XTAL1/TOSC1))
ENABLE: U1.9 (PD5(T1)); also elsewhere on the board
GND: C15.2, C16.2, C17.2, C18.2, C21.2, J1.6, Q2.2 (GND), R16.1, R17.1, R18.1, R24.1, S1.1, S1.2, U1.3 (GND), U1.5 (AGND), U1.21 (GND); also elsewhere on the board
I24_MEA: U1.24 (PC1(ADC1)); also elsewhere on the board
MISO: J1.1, U1.16 (PB4(MISO))
MOSI: J1.4, U1.15 (PB3(MOSI/OC2))
unnamed: FB1.2, U1.18 (AVCC)
unnamed: LED7.C, R16.2
unnamed: LED5.C, R18.2
unnamed: LED6.C, R17.2
unnamed: LED8.C, R24.2
RST: C15.1, J1.5, R15.1, S1.3, S1.4, U1.29 (PC6(/RESET))
SCK: J1.3, U1.17 (PB5(SCK))
SCL: R19.1, U1.28 (PC5(ADC5/SCL)); also elsewhere on the board
SDA: R20.1, U1.27 (PC4(ADC4/SDA)); also elsewhere on the board
TEMP_OUT: U1.26 (PC3(ADC3)); also elsewhere on the board
TEST1: LED6.A, U1.30 (PD0(RXD))
TEST2: LED5.A, U1.31 (PD1(TXD))
TEST3: LED7.A, U1.32 (PD2(INT0))
V24_MEA: U1.23 (PC0(ADC0)); also elsewhere on the board

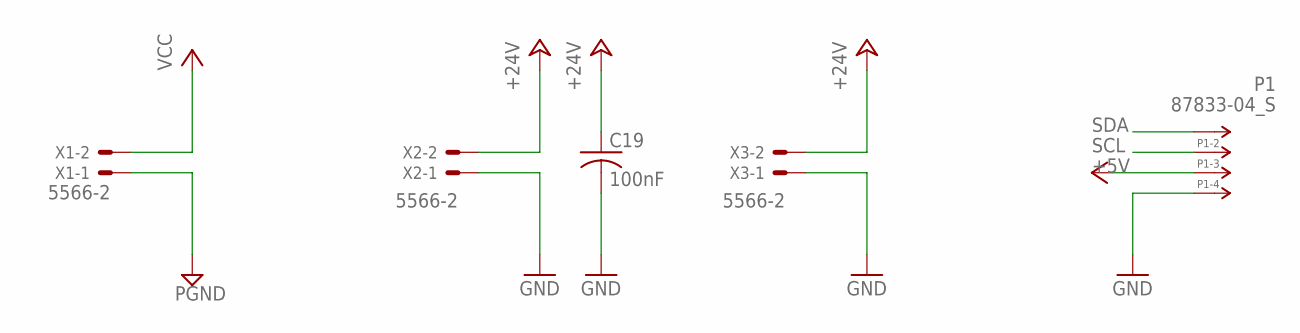
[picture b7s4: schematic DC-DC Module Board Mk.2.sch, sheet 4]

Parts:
C19: 100nF; C0603; PARTNO 445-5202-1-ND
P1: 87833-04_S; 87833-04; PARTNO WM18858-ND
X1, X2, X3: 5566-2; PARTNO WM23800-ND

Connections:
+5V: P1.3; also elsewhere on the board
+24V: C19.1, X2.2, X3.2; also elsewhere on the board
GND: C19.2, P1.4, X2.1, X3.1; also elsewhere on the board
GND1: X1.1; also elsewhere on the board
SCL: P1.2; also elsewhere on the board
SDA: P1.1; also elsewhere on the board
VCC: X1.2; also elsewhere on the board
